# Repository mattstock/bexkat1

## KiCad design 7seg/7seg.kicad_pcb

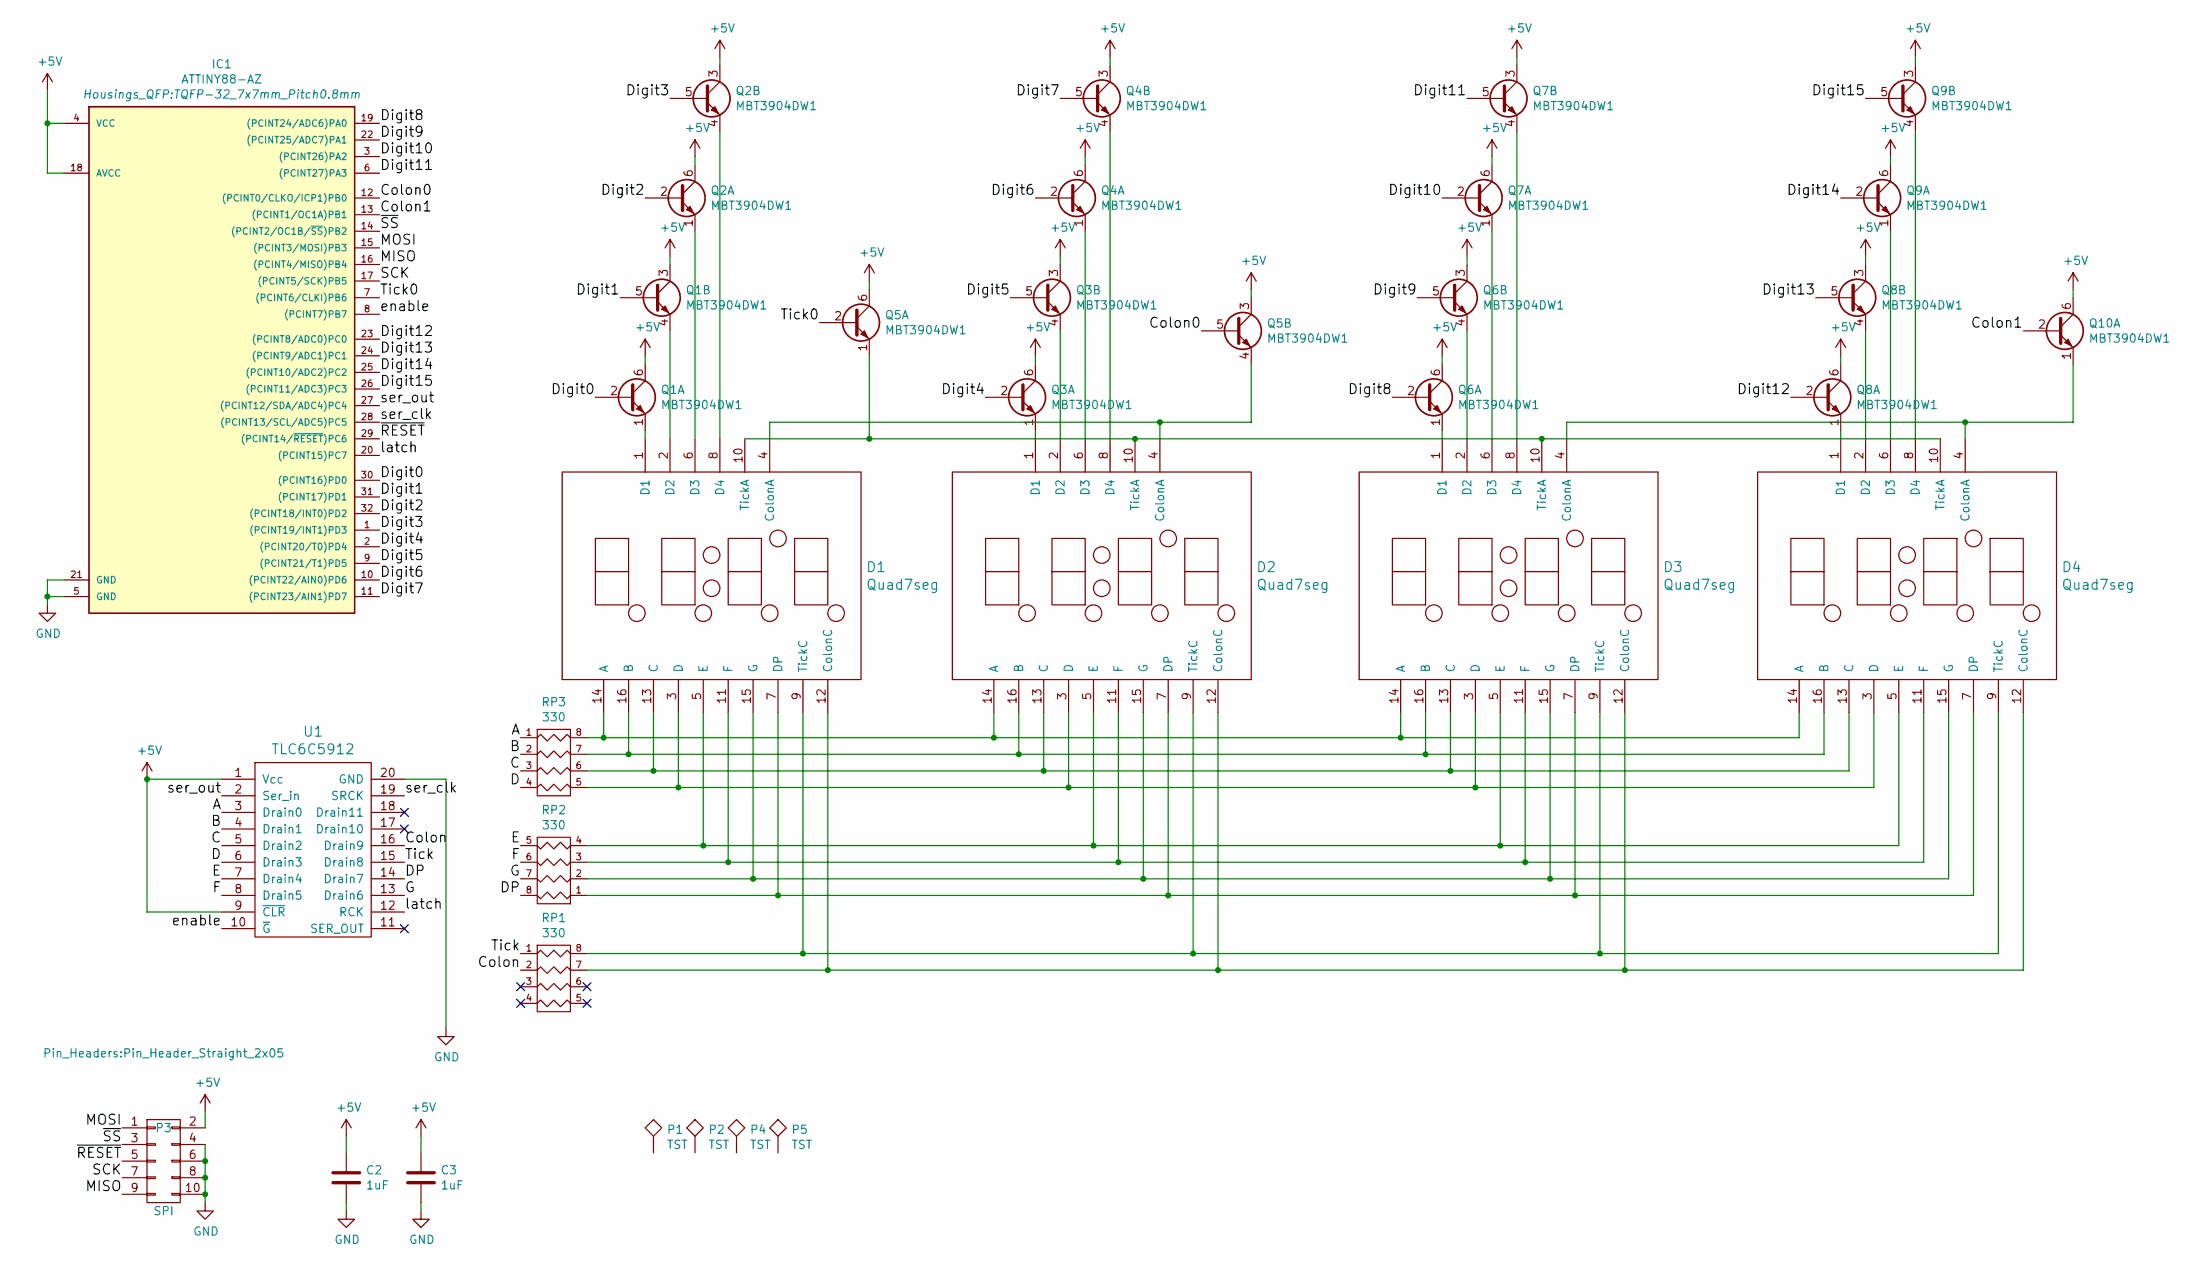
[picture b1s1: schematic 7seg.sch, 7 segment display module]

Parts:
C2, C3: 1uF; C_0805
D1, D2, D3, D4: Quad7seg; YSM-439AxxA-35
IC1: ATTINY88-AZ; TQFP-32_7x7mm_Pitch0.8mm
P1, P2, P4, P5: TST; SolderWirePad_single_2mmDrill
P3: SPI; Pin_Header_Straight_2x05
Q1, Q2, Q3, Q4, Q5, Q6, Q7, Q8, Q9, Q10: MBT3904DW1; SOT-363
RP1, RP2, RP3: 330; CAY16-J4
U1: TLC6C5912; TSSOP-20_4.4x6.5mm_Pitch0.65mm

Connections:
+5V: C2.1, C3.1, IC1.4 (VCC), IC1.18 (AVCC), P3.2, Q1.3 (C), Q1.6 (C), Q2.3 (C), Q2.6 (C), Q3.3 (C), Q3.6 (C), Q4.3 (C), Q4.6 (C), Q5.3 (C), Q5.6 (C), Q6.3 (C), Q6.6 (C), Q7.3 (C), Q7.6 (C), Q8.3 (C), Q8.6 (C), Q9.3 (C), Q9.6 (C), Q10.6 (C), U1.1 (Vcc), U1.9 (~CLR)
/A: RP3.1, U1.3 (Drain0)
/B: RP3.2, U1.4 (Drain1)
/C: RP3.3, U1.5 (Drain2)
/Colon: RP1.2, U1.16 (Drain9)
/Colon0: IC1.12 ((PCINT0/CLKO/ICP1)PB0), Q5.5 (B)
/Colon1: IC1.13 ((PCINT1/OC1A)PB1), Q10.2 (B)
/D: RP3.4, U1.6 (Drain3)
/DP: RP2.8 (R1), U1.14 (Drain7)
/Digit0: IC1.30 ((PCINT16)PD0), Q1.2 (B)
/Digit1: IC1.31 ((PCINT17)PD1), Q1.5 (B)
/Digit2: IC1.32 ((PCINT18/INT0)PD2), Q2.2 (B)
/Digit3: IC1.1 ((PCINT19/INT1)PD3), Q2.5 (B)
/Digit4: IC1.2 ((PCINT20/T0)PD4), Q3.2 (B)
/Digit5: IC1.9 ((PCINT21/T1)PD5), Q3.5 (B)
/Digit6: IC1.10 ((PCINT22/AIN0)PD6), Q4.2 (B)
/Digit7: IC1.11 ((PCINT23/AIN1)PD7), Q4.5 (B)
/Digit8: IC1.19 ((PCINT24/ADC6)PA0), Q6.2 (B)
/Digit9: IC1.22 ((PCINT25/ADC7)PA1), Q6.5 (B)
/Digit10: IC1.3 ((PCINT26)PA2), Q7.2 (B)
/Digit11: IC1.6 ((PCINT27)PA3), Q7.5 (B)
/Digit12: IC1.23 ((PCINT8/ADC0)PC0), Q8.2 (B)
/Digit13: IC1.24 ((PCINT9/ADC1)PC1), Q8.5 (B)
/Digit14: IC1.25 ((PCINT10/ADC2)PC2), Q9.2 (B)
/Digit15: IC1.26 ((PCINT11/ADC3)PC3), Q9.5 (B)
/E: RP2.5 (R4), U1.7 (Drain4)
/F: RP2.6 (R3), U1.8 (Drain5)
/G: RP2.7 (R2), U1.13 (Drain6)
/MISO: IC1.16 ((PCINT4/MISO)PB4), P3.9
/MOSI: IC1.15 ((PCINT3/MOSI)PB3), P3.1
/SCK: IC1.17 ((PCINT5/SCK)PB5), P3.7
/Tick: RP1.1, U1.15 (Drain8)
/Tick0: IC1.7 ((PCINT6/CLKI)PB6), Q5.2 (B)
/enable: IC1.8 ((PCINT7)PB7), U1.10 (~G)
/latch: IC1.20 ((PCINT15)PC7), U1.12 (RCK)
/ser_clk: IC1.28 ((PCINT13/SCL/ADC5)PC5), U1.19 (SRCK)
/ser_out: IC1.27 ((PCINT12/SDA/ADC4)PC4), U1.2 (Ser_in)
/~RESET: IC1.29 ((PCINT14/~RESET~)PC6), P3.5
/~SS: IC1.14 ((PCINT2/OC1B/~SS~)PB2), P3.3
GND: C2.2, C3.2, IC1.5 (GND), IC1.21 (GND), P3.4, P3.6, P3.8, P3.10, U1.20 (GND)
unnamed: D1.1 (D1), Q1.1 (E)
unnamed: D1.2 (D2), Q1.4 (E)
unnamed: D1.3 (D), D2.3 (D), D3.3 (D), D4.3 (D), RP3.5 (R4)
unnamed: D1.4 (ColonA), D2.4 (ColonA), Q5.4 (E)
unnamed: D1.5 (E), D2.5 (E), D3.5 (E), D4.5 (E), RP2.4
unnamed: D1.6 (D3), Q2.1 (E)
unnamed: D1.7 (DP), D2.7 (DP), D3.7 (DP), D4.7 (DP), RP2.1
unnamed: D1.8 (D4), Q2.4 (E)
unnamed: D1.9 (TickC), D2.9 (TickC), D3.9 (TickC), D4.9 (TickC), RP1.8 (R1)
unnamed: D1.10 (TickA), D2.10 (TickA), D3.10 (TickA), D4.10 (TickA), Q5.1 (E)
unnamed: D1.11 (F), D2.11 (F), D3.11 (F), D4.11 (F), RP2.3
unnamed: D1.12 (ColonC), D2.12 (ColonC), D3.12 (ColonC), D4.12 (ColonC), RP1.7 (R2)
unnamed: D1.13 (C), D2.13 (C), D3.13 (C), D4.13 (C), RP3.6 (R3)
unnamed: D1.14 (A), D2.14 (A), D3.14 (A), D4.14 (A), RP3.8 (R1)
unnamed: D1.15 (G), D2.15 (G), D3.15 (G), D4.15 (G), RP2.2
unnamed: D1.16 (B), D2.16 (B), D3.16 (B), D4.16 (B), RP3.7 (R2)
unnamed: D2.1 (D1), Q3.1 (E)
unnamed: D2.2 (D2), Q3.4 (E)
unnamed: D2.6 (D3), Q4.1 (E)
unnamed: D2.8 (D4), Q4.4 (E)
unnamed: D3.1 (D1), Q6.1 (E)
unnamed: D3.2 (D2), Q6.4 (E)
unnamed: D3.4 (ColonA), D4.4 (ColonA), Q10.1 (E)
unnamed: D3.6 (D3), Q7.1 (E)
unnamed: D3.8 (D4), Q7.4 (E)
unnamed: D4.1 (D1), Q8.1 (E)
unnamed: D4.2 (D2), Q8.4 (E)
unnamed: D4.6 (D3), Q9.1 (E)
unnamed: D4.8 (D4), Q9.4 (E)

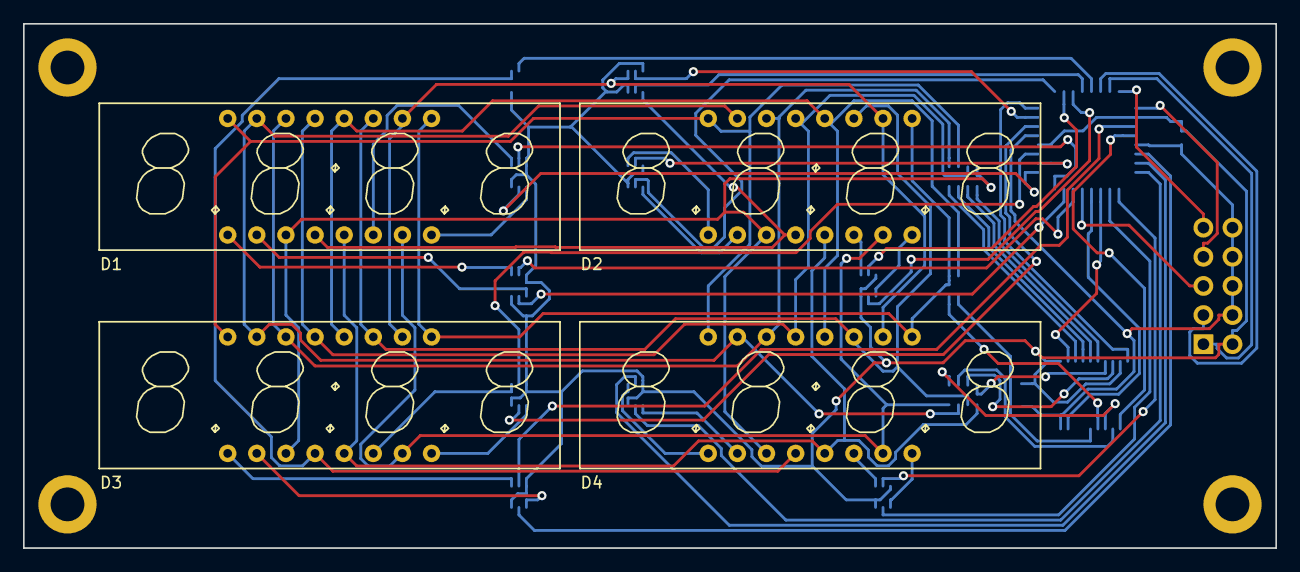
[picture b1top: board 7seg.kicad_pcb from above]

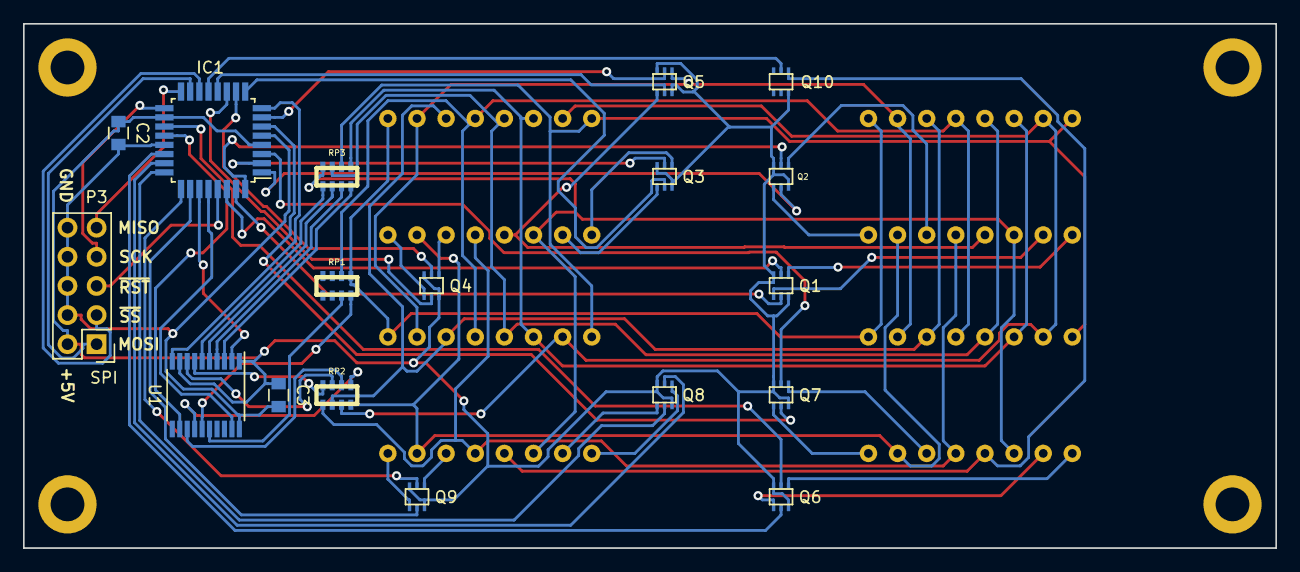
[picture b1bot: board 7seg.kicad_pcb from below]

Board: 2 copper layers, 109.2 x 45.7 mm, 26 parts (18 on the bottom side), 69 nets.

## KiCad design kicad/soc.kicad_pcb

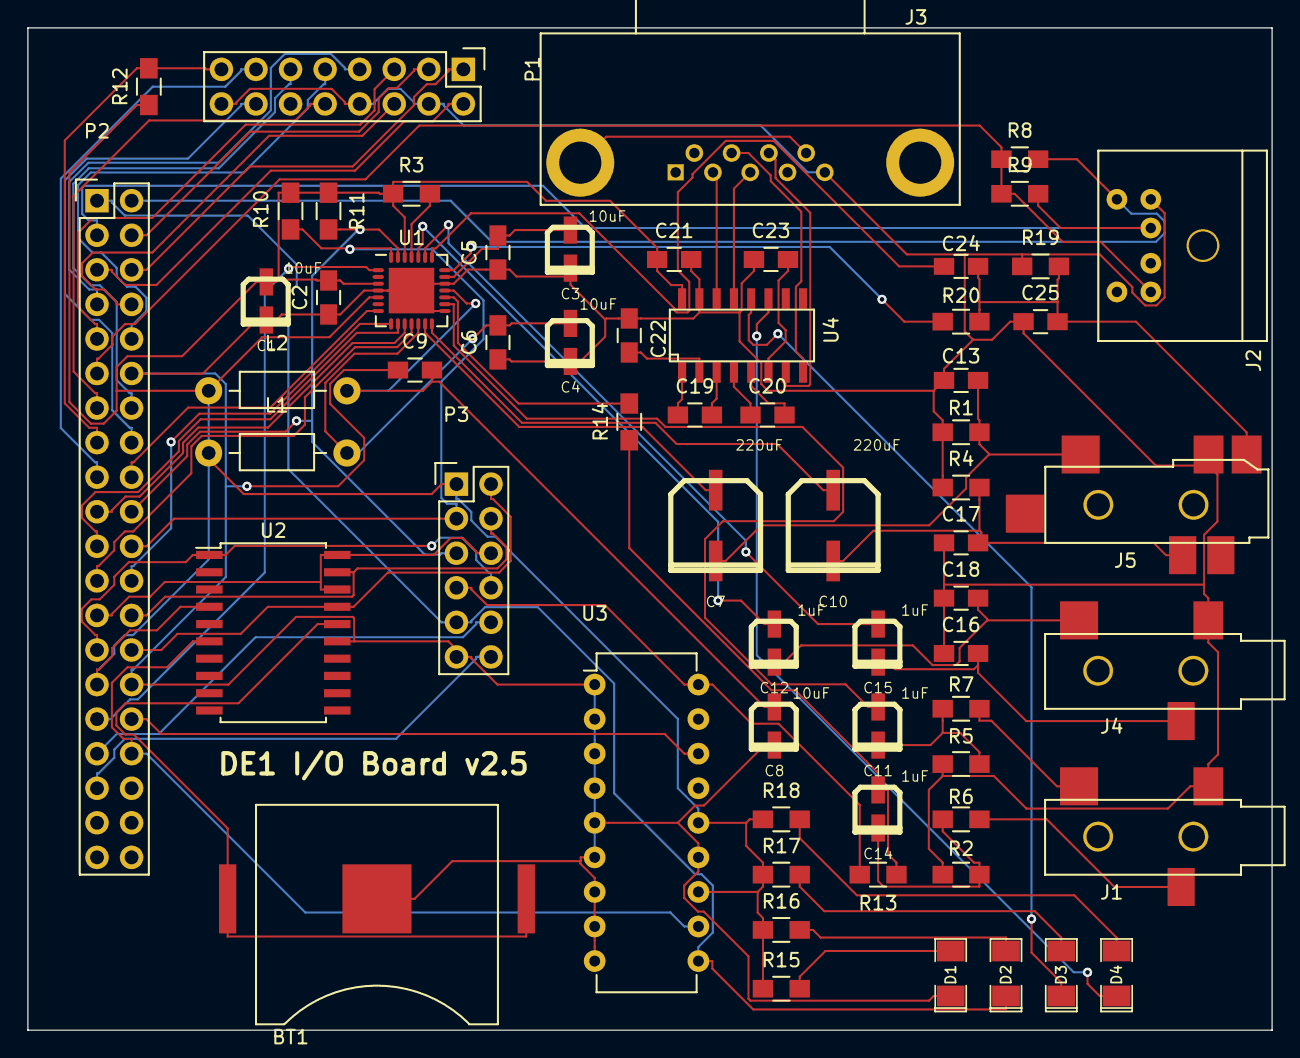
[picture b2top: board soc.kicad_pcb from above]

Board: 2 copper layers, 91.4 x 73.7 mm, 64 parts (0 on the bottom side), 74 nets.

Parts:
BT1: 2025 coin cell; coincell
C1, C3, C4, C8: 10uF; UWXCAP-3mm
C2, C5, C6, C9, C19, C20, C21, C22, C23: 0.1uF; C_0805_HandSoldering
C7, C10: 220uF; UWXCAP-6.3mm
C11, C12, C14, C15: 1uF; UWXCAP-3mm
C13, C16, C17, C18, C25: 220pF; C_0805_HandSoldering
C24: 1uF; C_0805_HandSoldering
D1: PWR; SM1206POL
D2: TX1; SM1206POL
D3: TX0; SM1206POL
D4: RX0; SM1206POL
J1: Line Out; SJ-352X-SMT
J2: PS/2 Keyboard; MD-60S
J3: DB9; DB9F
J4: Line In; SJ-352X-SMT
J5: Headphone; SJ-4351X-SMT
L1, L2: FB; Choke_Horizontal_RM10mm
P1: LED MATRIX; Pin_Header_Straight_2x08
P2: ALTERA_DE1_GPIO; Pin_Header_Straight_2x20
P3: IO; Pin_Header_Straight_2x06
R1, R2, R4, R5, R19: 47k; R_0805_HandSoldering
R3, R10, R11, R12: 100K; R_0805_HandSoldering
R6, R7, R20: 100; R_0805_HandSoldering
R8, R9: 1k; R_0805_HandSoldering
R13, R14: 10k; R_0805_HandSoldering
R15, R16, R17, R18: 330; R_0805_HandSoldering
U1: SSM2603; QFN-28-1EP_5x5mm_Pitch0.5mm
U2: DS3234; SOIC-20_7.5x12.8mm_Pitch1.27mm
U3: speakjet; DIP-18_W7.62mm
U4: MAX3232; SOIC-16

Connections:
+3V3: C1.1, C2.2, C21.1, L1.1, L2.1, P2.29, P3.1, R3.1, R10.1, R11.1, R12.1, R15.1, R16.1, R17.1, R18.1, U1.3, U1.5, U1.26, U2.4, U3.12, U3.14, U4.16
+5V: J2.4, P2.11, R8.1, R9.1
/A: P1.9, P2.10
/B: P1.10, P2.13
/B0: P1.3, P2.4
/B1: P1.7, P2.7
/BCLK: P2.18, U1.7
/C: P1.11, P2.14
/CLK: P1.13, P2.17
/G0: P1.2, P2.5
/G1: P1.6, P2.8
/GPIO1: P2.33, P3.10
/GPIO2: P2.35, P3.12
/Kbd_clk: J2.5, P2.2, R8.2
/Kbd_data: J2.1, P2.3, R9.2
/MCLK: P2.31, U1.1
/MISO_33: P2.26, P3.4, U2.19
/MOSI_33: P2.28, P3.2, U2.17
/PBDAT: P2.24, U1.8
/PBLRC: P2.21, U1.9
/R0: P1.1, P2.6
/R1: P1.5, P2.9
/RECDAT: P2.19, U1.10
/RECLRC: P2.23, U1.11
/SCLK: P2.22, P3.3, R10.2, U1.28
/SCLK_33: P2.25, P3.6, U2.18, U2.20
/SDIN: P2.20, P3.5, R11.2, U1.27
/STB: P1.14, P2.16
/Serial0_RX: D4.1, U4.11
/Serial0_TX: D3.1, U4.12
/Serial1_TX: D2.1, P2.1, P3.9, U3.10
/speaking: P2.32, U3.16
/voice: P3.7, R13.2, U3.18
/~OE: P1.15, P2.15, R12.2
/~RESET: P2.34, U2.6, U3.11
/~RTC_SS: P2.27, P3.8, U2.1
GND: BT1.2, C1.2, C2.1, C3.2, C4.2, C5.1, C6.1, C8.2, C9.1, C13.1, C16.1, C17.1, C18.1, C21.2, C22.1, C23.1, C25.1, D1.1, J1.1, J2.3, J3.5, J4.1, J5.4, P1.4, P1.8, P1.16, P2.12, P2.30, P3.11, R1.1, R2.1, R4.1, R5.1, R19.1, U1.4, U1.15, U1.19, U1.29, U2.15, U3.1, U3.2, U3.3, U3.4, U3.5, U3.6, U3.7, U3.8, U3.9, U3.13, U4.15
unnamed: BT1.1, U2.16
unnamed: C3.1, C5.2, U1.20
unnamed: C4.1, C6.2, L1.2, U1.12
unnamed: C7.1, U1.13
unnamed: C8.1, C9.2, L2.2, U1.18
unnamed: C10.1, U1.14
unnamed: C10.2, C17.2, J5.3, R4.2
unnamed: C11.1, U1.16
unnamed: C11.2, R5.2, R7.2
unnamed: C12.1, U1.24
unnamed: C12.2, C18.2, J4.2
unnamed: C7.2, C13.2, J5.2, R1.2
unnamed: C14.1, R13.1, R14.1
unnamed: C14.2, R2.2, R6.2
unnamed: C15.1, U1.23
unnamed: C15.2, C16.2, J4.3
unnamed: C19.1, U4.1
unnamed: C19.2, U4.3
unnamed: C20.1, U4.4
unnamed: C20.2, U4.5
unnamed: C22.2, U4.2
unnamed: C23.2, U4.6
unnamed: C24.1, C25.2, J5.1, R19.2, R20.1
unnamed: C24.2, U1.22
unnamed: D1.2, R15.2
unnamed: D2.2, R16.2
unnamed: D3.2, R17.2
unnamed: D4.2, R18.2
unnamed: J1.2, R7.1
unnamed: J1.3, R6.1
unnamed: J3.2, U4.14
unnamed: J3.3, U4.13
unnamed: J3.7, U4.8
unnamed: J3.8, U4.7
unnamed: R3.2, U1.25
unnamed: R14.2, U1.17
unnamed: R20.2, U1.21

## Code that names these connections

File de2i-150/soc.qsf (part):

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set_instance_assignment -name IO_STANDARD "2.5 V" -to SW[3]
set_instance_assignment -name IO_STANDARD "2.5 V" -to SW[2]
set_instance_assignment -name IO_STANDARD "2.5 V" -to SW[1]
set_location_assignment PIN_B27 -to serial0_rx
set_location_assignment PIN_H24 -to serial0_tx
set_location_assignment PIN_AG19 -to fl_ce_n
set_location_assignment PIN_AJ19 -to fl_oe_n
set_location_assignment PIN_AG18 -to fl_rst_n
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set_location_assignment PIN_AF18 -to sd_mosi
set_location_assignment PIN_AE18 -to sd_ss
set_location_assignment PIN_AH25 -to sd_sclk
set_location_assignment PIN_G22 -to rtc_ss
set_location_assignment PIN_K21 -to matrix0[2]
set_location_assignment PIN_D19 -to matrix0[1]
set_location_assignment PIN_F18 -to matrix0[0]
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set_instance_assignment -name WEAK_PULL_UP_RESISTOR ON -to codec_sclk
set_instance_assignment -name WEAK_PULL_UP_RESISTOR ON -to codec_sdin
set_location_assignment PIN_AH28 -to irda_rxd
set_location_assignment PIN_G16 -to serial1_tx
set_location_assignment PIN_B15 -to td_clk27
set_location_assignment PIN_K17 -to td_data[7]
set_location_assignment PIN_K18 -to td_data[6]
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
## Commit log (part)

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2015-05-17 start of some vararg testing
2015-05-17 clean up trivial warning
2015-06-03 more tests with gcc
2015-06-07 fix bug in address decode
2015-06-08 improved test cases, update to _start to support gcc
2015-06-14 use new gcc
2015-06-14 added new targets and linker script for now
2015-06-14 add use of regular gcc w/o the gcc support files. Need this until we sort out the linker scripts and other stuff.
2015-06-14 added basic hw support for ITDB02 lcd/touchscreen/sd interface
2015-06-15 itd spi skeleton
2015-06-17 sped up the SPI interface to about 8MHz-ish
2015-07-02 additional work to try to get ssram working.
2015-07-03 improved simple _start
2015-07-03 partial working
2015-07-06 flash memory added to map and the beginnings of an SDRAM controller.
2015-07-12 fix for ssram access
2015-07-14 start to CPU support for interrupts and fault handling
2015-07-14 some work on schematic incorporating the lcd touchscreen
2015-08-07 add register relative jsr opcode
2015-08-07 updated testing
2015-08-07 build pretty for bootloader and add elf support for monitor
2015-08-08 a basic font
2015-08-31 progress debugging complex newlib gcc issues
2015-09-04 fix missing matrix cleanup
2015-09-05 more tests
2015-09-05 demo of font generation on matrix and LCD
2015-09-06 another basic test program
2015-09-06 add SW17 as vector write-enable
2015-09-14 add setint and implement trap, refactor exception and interrupt handling slightly
2015-09-21 first shot at external and internal interrupt vector handling
2015-09-27 add tx and rx buffer for uart
2015-09-28 finish refactor of CCR
2015-09-30 some additional fp tests
2015-10-05 overhaul floating point ops for double precision. some additional testing and implementation needed, but int operations look ok.
2015-10-07 small cleanup on a known working config
2015-10-09 finalize floating point support, add sqrt.s opcode, and start to build custom mandelbrot hardware module
2015-10-16 add more fatfs features and reduce the storage of the bootstrap
2015-10-19 refactoring of the bus interface
2015-10-25 working vga implementation 640x480 512 colors (3x3x3)
2015-10-28 update fatfs lib to use spi functions and macros
2015-10-28 fix typo in video output selection
2015-10-29 brownout protection
2015-10-31 some additional test programs
2015-10-31 fix zeroing of BSS
2015-11-01 fix read timings for matrix
2015-11-02 initial cut of simple sdram controller
2015-11-02 expanded memory testing
2015-11-03 cleanup of SDRAM address map
2015-11-04 fix to SPI to support multiple modes properly
2015-11-07 some file tests with libgloss
2015-11-08 small adjustments to SPI and other stuff
2015-11-09 update of memory map to use sdram, and move the io system and led matrix out of the way
2015-11-09 some changes to support the touchscreen input line as well as the SPI ADC for the joystick
2015-11-15 still testing best vga memory interface options
2015-11-22 working VGA interface with pallette bootstrap
2015-11-24 working palette mapped VGA mode
2015-11-26 don't save when you still have the files open
2015-12-03 clean up thresholds
2015-12-10 update the timing data and fix a minor warning
2015-12-12 initial test framework for CPU
2015-12-13 add register to alu output
2015-12-13 more cleanup
2015-12-15 some additional control cleanup
2015-12-18 change opcodes for integer ops to align with true module codes
2015-12-25 First pass at optimized ISA and control structures. Not everything is tested and working, however enough is functional to allow the bootstrap to initialize and run programs from the microSD.
2015-12-26 add support for bsr opcode
2015-12-27 fix IO addressing
2015-12-28 start of additional VGA options
2015-12-29 enabled dual VGA mode support using the control register
2016-01-03 add enable/disable of cache functions, implement a test ROM to run regressions against the system to detect anomalous behavior.
2016-01-04 fixed cache bug, added some additional debug support
2016-01-04 fixed a bug in SPI code for non-mode 0 operations as well as corrections to the RTC code
2016-01-05 prep for text video modes
2016-01-05 more support functions and tests
2016-01-06 split out support library to use for both libgloss as well as standalone applications
2016-01-06 fib test back to normal
2016-01-06 fix vga mode change and addressing ranges
2016-01-08 add additional speeds for SPI, full codec support
2016-01-15 some kicad stuff
2016-01-29 one step closer to working sdram on de1
2016-02-01 improved typing which keeps the register addresses in the correct section.
2016-02-01 functional caching and with adaptor for de1... I hope.
2016-02-05 some random stuff I forgot about
2016-02-05 small cleanups
2016-02-06 close to final
2016-02-06 more board tweaks
2016-02-14 version for PCB
2016-04-03 updates to support board
2016-04-18 some work on demo programs
2016-04-23 add sin computing function
2016-04-26 add basic bmp display support
2016-05-01 work on mandelbrot accelerator
2016-05-04 working hardware implementation, but it looks like memory costs swamp the simple math functions in registers. need to look at implementing the interatior within the hardware as well.
2016-05-06 functioning mandelbrot hardware accelerator, including the iterative portion. probably can add a check for infinity to reduce the iteration count but not today.
2016-10-09 new I/O board to test SSM2603 codec
2016-10-20 some pcie attempt
2016-11-20 nak handling
2016-11-20 start of IO board changes
2016-11-25 more work on new IO board
2016-11-26 working i2c interface and example codec programming
2016-11-26 up core clock to 100MHz. Some VGA tearing due to bus contention still needs to be dealt with.
2016-11-27 fix ssram timing
2016-11-27 consolidated PLLs, removed delay in SSRAM writes
2016-11-30 up quartus rev
2016-12-01 add write fifo for SDRAM cache
2016-12-02 increase L1 cache to 4k words
2016-12-02 new pipeline still not working
2016-12-04 more refined tests, for a more civilized age
2016-12-04 working pipeline sdram
2016-12-04 adjust self tests
2016-12-05 progress on max10 refactoring
2016-12-11 adjust for new locations
2016-12-13 fix matrix pinout
2016-12-16 add new kicad file
2016-12-17 additions to the support board
2016-12-17 refactor vga in preparation for a text modem driver
2016-12-18 fix dumb write bug in bootstrap
2016-12-18 simple cleanups
2016-12-18 update PLL for codec
2016-12-19 adding mic input
2016-12-20 updated base font
2016-12-20 Revert "Revert "updated base font""
    This reverts commit 1c20ee986e71a34df52feae900f46b41d67a4191.
2016-12-21 fixed most of the combinatorial chain problems in the textmode controller. Synthesized modulus killed things pretty badly.
2016-12-22 fixes to SSRAM controller
2016-12-22 cleanup VGA functions
2016-12-23 added color text modes
2016-12-23 refactor vga controls to make it easier to optimize
2016-12-23 building on the vga library functions and test OS, plus a few small fixes in the SOC vga controller logic
2016-12-24 expose cache counters in memory map
2016-12-24 2 way cache passes tests, but doom is acting odd? need to do some regression checks.
2016-12-29 set up support for basic supervisor mode. Need to implement opcodes to allow privs to be lowered before we can test for sure, and then add mmu support.
2016-12-29 new opcodes to support supervisor mode
2016-12-31 refactoring to run applications in user mode. currently disabled the fat filesysem in user code due to the need to handle the timer interrupts. This tracks with a similar set of changes in the libglo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
2017-01-02 add support for write faults to ROM
2017-01-07 finish pcb rev
2017-01-08 refactor roms into common bios module
2017-01-12 work on 7 segment display module
2017-01-15 improved timer functions
2017-01-17 slow down fam speed
2017-01-17 update some of the vga lib
2017-01-18 spin 7seg board and io 2.5
2017-01-21 boostrap is failing to load image likely due to linker issues
2017-01-21 add printf support to the vga and serial libraries without dragging in all of stdio
2017-01-21 some crude serial ANSI support
2017-01-22 apply all of the good linker bits for max10 as well
2017-01-22 move VGA console to use ps2 keyboard and build simple scan code to ascii implementation
2017-01-22 correct versioning on schematic
2017-01-31 incorporate io board serial port as port 2, fix up SPI to be able to support an additional slave select on the io board, working forimware for the 7seg board, and small fixups for the IO board schema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
2017-03-11 minor cleanups, refactor bus interface, add some testing for ethernet phy
2017-05-04 small updates
2017-05-06 some more work on the firmware
2017-05-07 fixed command syncronization
2017-05-07 Need to read up on kicad changes but I think this is needed now.
2017-05-07 quiet git down
2017-10-08 update to new version of quartus as well as refactored VGA controller
2017-10-11 upgrade of quartus IP and maybe almost working video
2017-10-11 more IP upgrades
2018-01-02 updates for quartus mostly
2018-01-02 rebaseline for new quartus
2018-01-03 scratch work
2018-01-03 move circle script
2018-01-05 more adjustments
2018-01-06 remove old project
2018-01-07 mmu is busted
2018-03-20 pipelined CPU working with serial port and ROM. No RAM yet.
2018-03-25 remove sdram from the loop to validate ram behaviors
2018-04-14 remove old style vectors memory
2018-04-16 tests are still failing, but I'm getting closer
2018-04-16 use the common mmu module
2018-04-18 fix test case code
2018-04-18 update the logic analysis
2018-05-06 updates to the max10 project
2018-05-14 better tests
2018-05-19 add some support for a bus exception
2018-05-27 move to the DECA board
2018-07-22 some stuff we want to save
2018-07-22 debug changes
2018-10-30 checkin of base
2018-11-13 tweaking the firmware tests
2018-11-18 changed serial pinout to support arduino shield and the use of gpio for other functions
2018-11-22 working around odd issue with STARTUP in the linker script
2018-11-22 some changes to help with testing and fixed accidenal ROMing of RAM
2018-12-16 almost working sdram logic
2018-12-17 sdram testing
2018-12-28 remove some more old cruft
2018-12-29 update the slave select lines
2018-12-29 improved makefile
2018-12-30 clean up some of the peripherals in the address apce
2018-12-30 updates to support new peripheral setup
2018-12-31 some updated tests
2018-12-31 remove all of the old test programs from the default build
2018-12-31 more progress
2019-01-12 starting to work on vga
2019-01-13 clean up old test files
2019-01-13 apply dualram module everywhere
2019-01-20 some additional chipping at the vga logic
2019-08-04 update to new core for vga
2019-08-04 starting to set up port for de10-standard
2019-08-06 mostly good looking pin assignments
2019-08-11 additional testing of de10-standard
2019-08-26 update for max10s
2019-12-27 max10-lite update to 19.1 quartus
2019-12-27 de2i-150 update to quartus 19.1
2019-12-28 some refactoring work to allow for use of multiple dev boards and isolate the IP
2019-12-29 start of SPI additions
2019-12-31 improve debugging
2019-12-31 working SD card
2020-01-05 update to use named sdcard
2020-01-06 correct for new register map
2020-01-07 working ANSI hex editor
2020-01-08 increment the memory pages correctly
2020-01-25 shrink the size of the scratch ram and increase the rom
2020-01-25 move ps2 to supported section
2020-01-25 add some limited timing support
2020-01-25 update to use new modules and expanded set of logic captures

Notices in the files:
de2i-150/soc.qsf:
Copyright (C) 1991-2012 Altera Corporation
